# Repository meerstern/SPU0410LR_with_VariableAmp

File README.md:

# 可変アンプ内蔵アナログ出力MEMSマイク変換基板
SPU0410LR_with_VariableAmp  
The Converter board of Kicad Data for SPU0410LR with Variable Apmlifer

## 概要
最大約50倍の増幅回路[TLV316][0]とKnowles社製[アナログ出力MEMSマイクSPU0410LR5H][1]を搭載した2.54mmピッチ変換基板です。  
可聴音から超音波(100Hz～80kHz)までの幅広い帯域を高感度にセンシングすることが可能です。  
超音波センサや超音波通信などに使用可能です。  
RV1により約1倍～約50倍まで変更することが可能です。  
アンプ回路を搭載することでArduinoといったマイコンのアナログ入力に直接接続できます。  
マイク穴は基板裏面の丸印部分です。  
電源電圧1.8V~3.6V

## 超音波マイク比較
 用途に応じて様々な製品をラインアップしています  
| 製品名 | インタフェース | アンプ搭載有無 | 用途 | 
|:-----------|:------------|:------------|:------------|
| [アナログ出力マイク][A] | アナログ | 無 | 任意のアンプ回路を使用したい場合 | 
| [可変アンプ内蔵アナログ出力マイク(本製品)][B] | アナログ | 有(可変1~50倍) | 増幅率の調整が必要な場合 |	
| [アンプ内蔵アナログ出力マイク][C] |	アナログ | 有(固定50倍) | 一定した増幅が必要な場合	| 
| [デジタル出力マイク][D] |	デジタルPDM | 不要 | フルデジタルで実装する場合やワイドレンジが必要な場合 | 

## 販売サイト
  * [スイッチサイエンス][2]

## 告知
SPU0410LR5Hの生産完了に伴い、弊社在庫がなくなり次第、後継品のSPV0142LR5Hに移行予定(25年秋~26年春頃)です。

License - MIT

[1]: https://www.digikey.jp/product-detail/ja/knowles/SPU0410LR5H-QB-7/423-1139-1-ND/2420983 "*1"
[0]: http://www.tij.co.jp/product/jp/TLV316 "*0"
[2]: https://www.switch-science.com/products/6583

[A]: https://github.com/meerstern/SPU0410LR
[B]: https://github.com/meerstern/SPU0410LR_with_Amp
[C]: https://github.com/meerstern/SPU0410LR_with_VariableAmp
[D]: https://github.com/meerstern/SPH0641LU

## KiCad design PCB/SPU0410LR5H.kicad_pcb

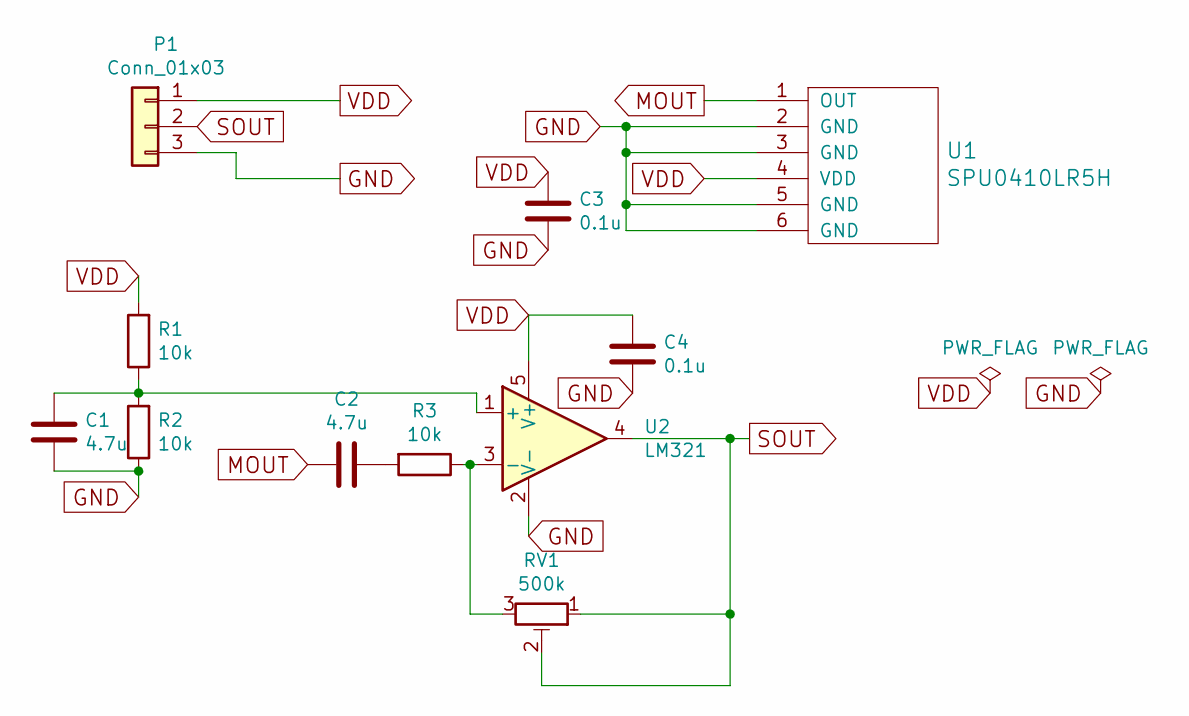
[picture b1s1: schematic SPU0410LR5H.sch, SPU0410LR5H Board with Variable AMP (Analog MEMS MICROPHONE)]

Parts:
C1, C2: 4.7u; generic-SMD1608
C3: 0.1u; C-1206
C4: 0.1u; generic-SMD1608
P1: Conn_01x03; pinhead-1X03
R1, R2, R3: 10k; generic-SMD1608
RV1: 500k; rcl-RTRIMCVR42A
U1: SPU0410LR5H
U2: LM321; SC-70-5

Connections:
GND: C1.2, C3.2, C4.2, P1.3, R2.1, U1.2 (GND), U1.3 (GND), U1.5 (GND), U1.6 (GND), U2.2 (V-)
MOUT: C2.2, U1.1 (OUT)
unnamed: C1.1, R1.1, R2.2, U2.1 (+)
unnamed: C2.1, R3.2
unnamed: R3.1, RV1.3, U2.3 (-)
SOUT: P1.2, RV1.1, RV1.2, U2.4
VDD: C3.1, C4.1, P1.1, R1.2, U1.4 (VDD), U2.5 (V+)

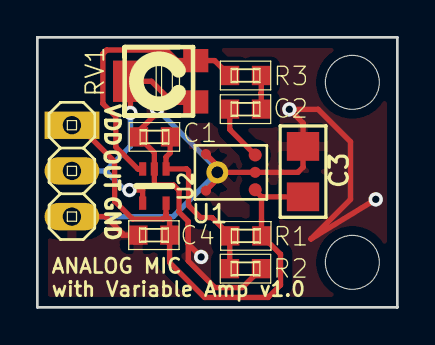
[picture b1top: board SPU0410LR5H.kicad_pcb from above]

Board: 2 copper layers, 20.0 x 15.0 mm, 13 parts (0 on the bottom side), 7 nets.

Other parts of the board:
REF1, REF2: MountingHole_3mm

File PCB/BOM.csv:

Elecrow PN,Parts,Value,Package,QTY,Digikey/Mouser/Manufacturer Part,Remark/ Link
,U1,SPU0410LR5H,SPU0410LR5H,1,423-1139-1-ND,https://www.digikey.jp/product-detail/ja/knowles/SPU0410LR5H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
C19666,"C2,C1",4.7u,SMD0603,2,,
,C3,0.1u,SMD1206,1,490-1767-1-ND ,https://www.digikey.jp/product-detail/ja/murata-electronics-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
C14663,C4,0.1u,SMD0603,1,,
C25804,"R1,R2,R3",10k,SMD0603,3,,
C23192,R4,510k,SMD0603,1,,
,U2,TLV316,SC-70-5,1,296-47313-1-ND,https://www.digikey.jp/product-detail/ja/texas-instruments/T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

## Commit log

2020-09-06 Add files
2020-09-06 Add images
2020-09-06 Add README
2022-12-06 Add shop link
